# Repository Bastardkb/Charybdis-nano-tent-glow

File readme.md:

## Midglow plate

Charybdis Nano mod to add lights to the bottom plate when using the 30 degree organic tents.

## Required parts

### PCB

Order the PCB in 1mm thickness.
The gerber can be found in the releases section.

### Middle layer

The files are in the `mechanical` folder.

You have 2 options :

- print the STL in transparent PLA/PETG
- laser-cut an acrylic sheet (use the dxf)

### Bottom layer

Use the bottom plates for the tents from the Charybdis repo. Either 3d print or laser cut.

### Screws etc

The parts are for one side. If building a double Charybdis Nano, double the parts.

| Part name                                    | Amount |
| -------------------------------------------- | ------ |
| M4 8mm Torx Screw                            | 2      |
| M4 Nut                                       | 2      |
| PCB                                          | 1      |
| 3d printed or laser cut acrylic middle layer | 1      |
| 1206 resistor, 330 Ohms                      | 1      |
| 1206 capacitor, 1uF                          | 1      |
| SK6812 Mini_e led                            | 15     |

## License

This work is licensed under a Creative Commons Attribution-NonCommercial-ShareAlike 4.0 International License.

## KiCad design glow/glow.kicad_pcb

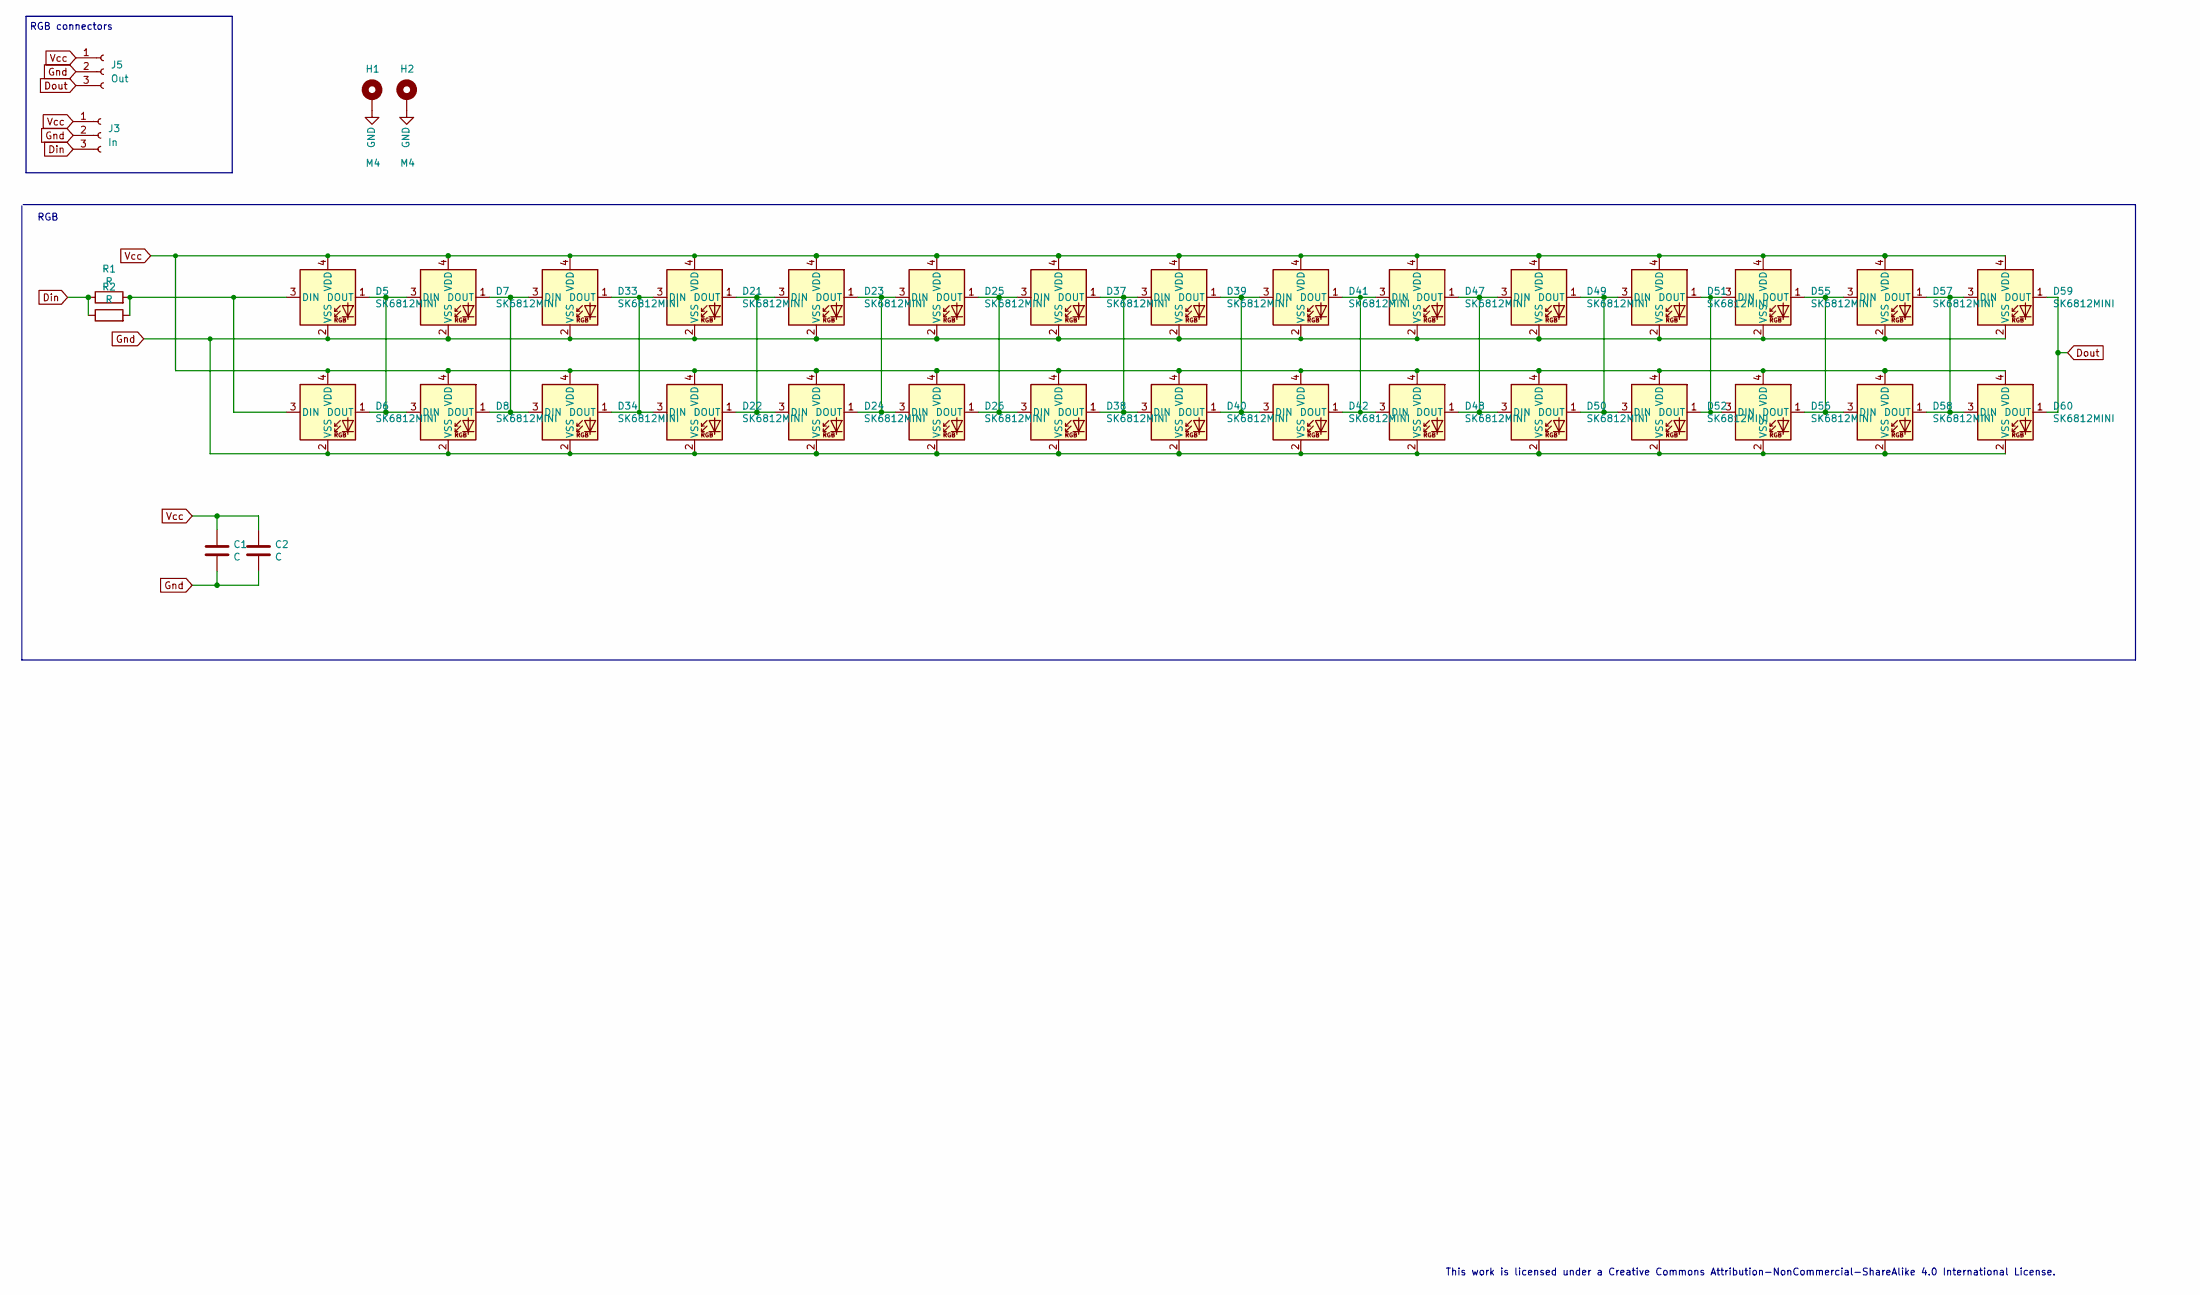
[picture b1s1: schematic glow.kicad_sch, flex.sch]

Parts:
C1, C2: C; C_1206_3216Metric_Pad1.42x1.75mm_HandSolder
D5, D7, D21, D23, D25, D33, D37, D39, D41, D47, D49, D51, D55, D57, D59: SK6812MINI; YS-SK6812MINI-E_REVERSE
D6, D8, D22, D24, D26, D34, D38, D40, D42, D48, D50, D52, D56, D58, D60: SK6812MINI; YS-SK6812MINI-E_REVERSE_NO_EDGECUT
H1, H2: M4; MountingHole_4mm_Pad_Via
J3: In; PinHeader_1x03_P2.54mm_Vertical
J5: Out; PinHeader_1x03_P2.54mm_Vertical
R1, R2: R; R_1206_3216Metric_Pad1.42x1.75mm_HandSolder

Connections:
Din: J3.3, R1.1, R2.1
Dout: D59.1 (DOUT), D60.1 (DOUT), J5.3
GND: H1.1, H2.1
Gnd: C1.2, C2.2, D5.2 (VSS), D6.2 (VSS), D7.2 (VSS), D8.2 (VSS), D21.2 (VSS), D22.2 (VSS), D23.2 (VSS), D24.2 (VSS), D25.2 (VSS), D26.2 (VSS), D33.2 (VSS), D34.2 (VSS), D37.2 (VSS), D38.2 (VSS), D39.2 (VSS), D40.2 (VSS), D41.2 (VSS), D42.2 (VSS), D47.2 (VSS), D48.2 (VSS), D49.2 (VSS), D50.2 (VSS), D51.2 (VSS), D52.2 (VSS), D55.2 (VSS), D56.2 (VSS), D57.2 (VSS), D58.2 (VSS), D59.2 (VSS), D60.2 (VSS), J3.2, J5.2
unnamed: D5.1 (DOUT), D6.1 (DOUT), D7.3 (DIN), D8.3 (DIN)
unnamed: D21.1 (DOUT), D22.1 (DOUT), D23.3 (DIN), D24.3 (DIN)
unnamed: D23.1 (DOUT), D24.1 (DOUT), D25.3 (DIN), D26.3 (DIN)
unnamed: D25.1 (DOUT), D26.1 (DOUT), D37.3 (DIN), D38.3 (DIN)
unnamed: D7.1 (DOUT), D8.1 (DOUT), D33.3 (DIN), D34.3 (DIN)
unnamed: D21.3 (DIN), D22.3 (DIN), D33.1 (DOUT), D34.1 (DOUT)
unnamed: D37.1 (DOUT), D38.1 (DOUT), D39.3 (DIN), D40.3 (DIN)
unnamed: D39.1 (DOUT), D40.1 (DOUT), D41.3 (DIN), D42.3 (DIN)
unnamed: D41.1 (DOUT), D42.1 (DOUT), D47.3 (DIN), D48.3 (DIN)
unnamed: D47.1 (DOUT), D48.1 (DOUT), D49.3 (DIN), D50.3 (DIN)
unnamed: D49.1 (DOUT), D50.1 (DOUT), D51.3 (DIN), D52.3 (DIN)
unnamed: D51.1 (DOUT), D52.1 (DOUT), D55.3 (DIN), D56.3 (DIN)
unnamed: D55.1 (DOUT), D56.1 (DOUT), D57.3 (DIN), D58.3 (DIN)
unnamed: D57.1 (DOUT), D58.1 (DOUT), D59.3 (DIN), D60.3 (DIN)
unnamed: D5.3 (DIN), D6.3 (DIN), R1.2, R2.2
Vcc: C1.1, C2.1, D5.4 (VDD), D6.4 (VDD), D7.4 (VDD), D8.4 (VDD), D21.4 (VDD), D22.4 (VDD), D23.4 (VDD), D24.4 (VDD), D25.4 (VDD), D26.4 (VDD), D33.4 (VDD), D34.4 (VDD), D37.4 (VDD), D38.4 (VDD), D39.4 (VDD), D40.4 (VDD), D41.4 (VDD), D42.4 (VDD), D47.4 (VDD), D48.4 (VDD), D49.4 (VDD), D50.4 (VDD), D51.4 (VDD), D52.4 (VDD), D55.4 (VDD), D56.4 (VDD), D57.4 (VDD), D58.4 (VDD), D59.4 (VDD), D60.4 (VDD), J3.1, J5.1

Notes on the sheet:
RGB connectors
RGB
This work is licensed under a Creative Commons Attribution-NonCommercial-ShareAlike 4.0 International License.

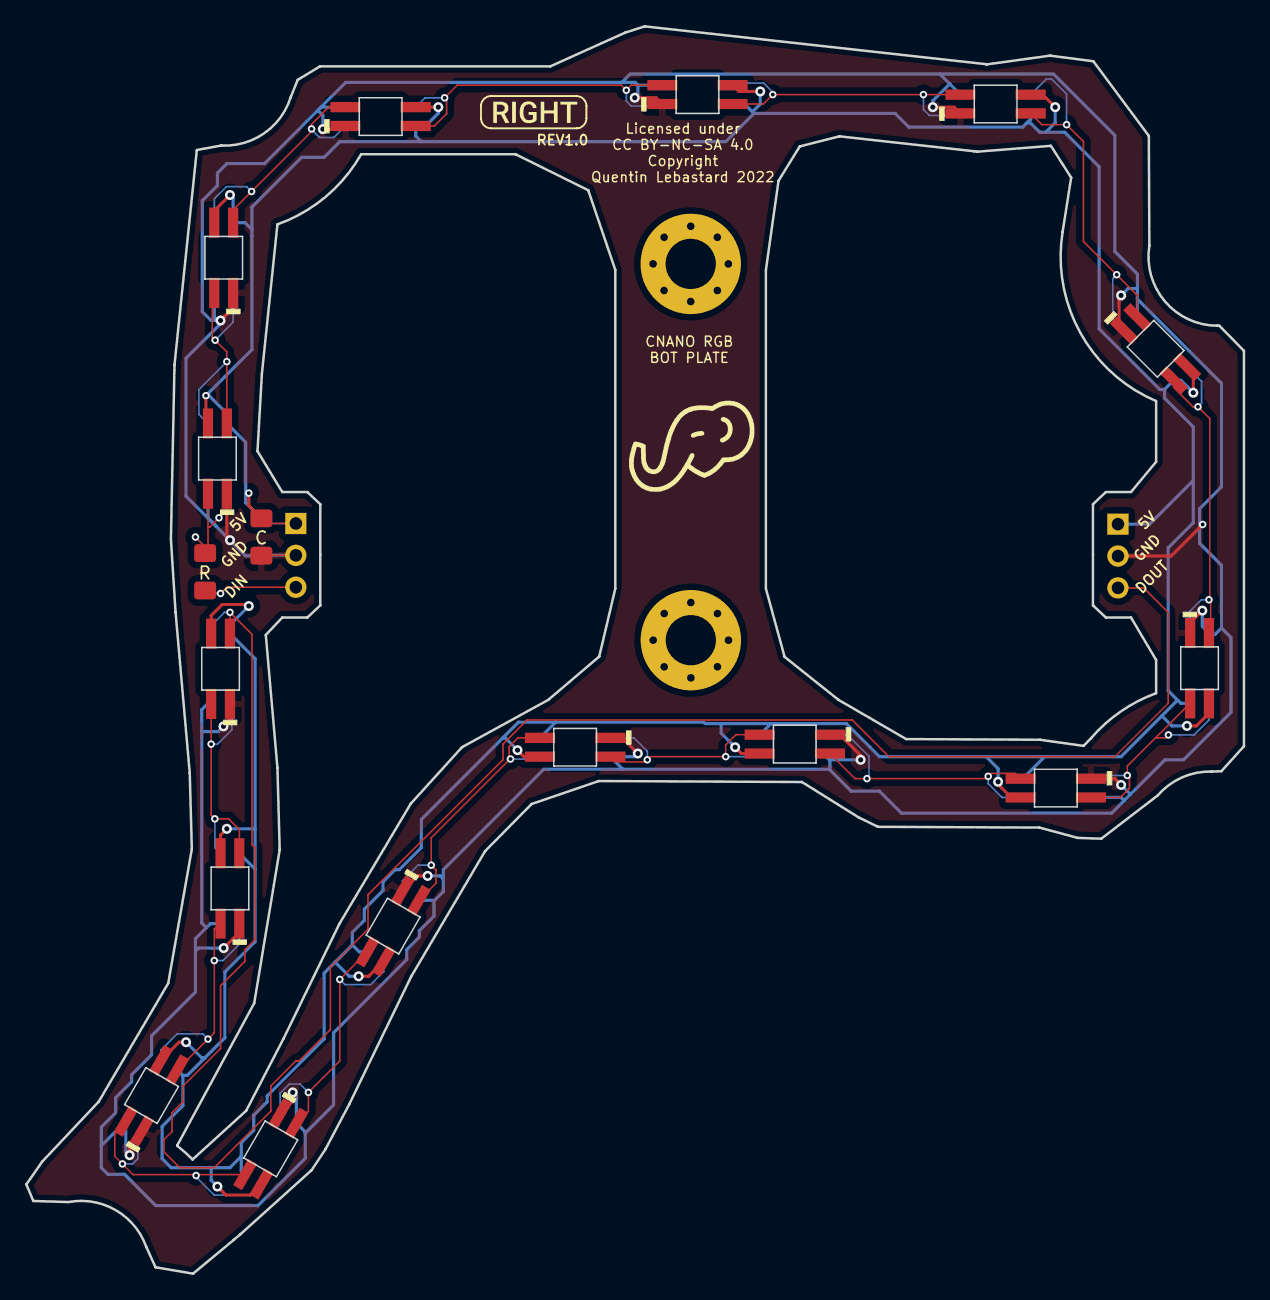
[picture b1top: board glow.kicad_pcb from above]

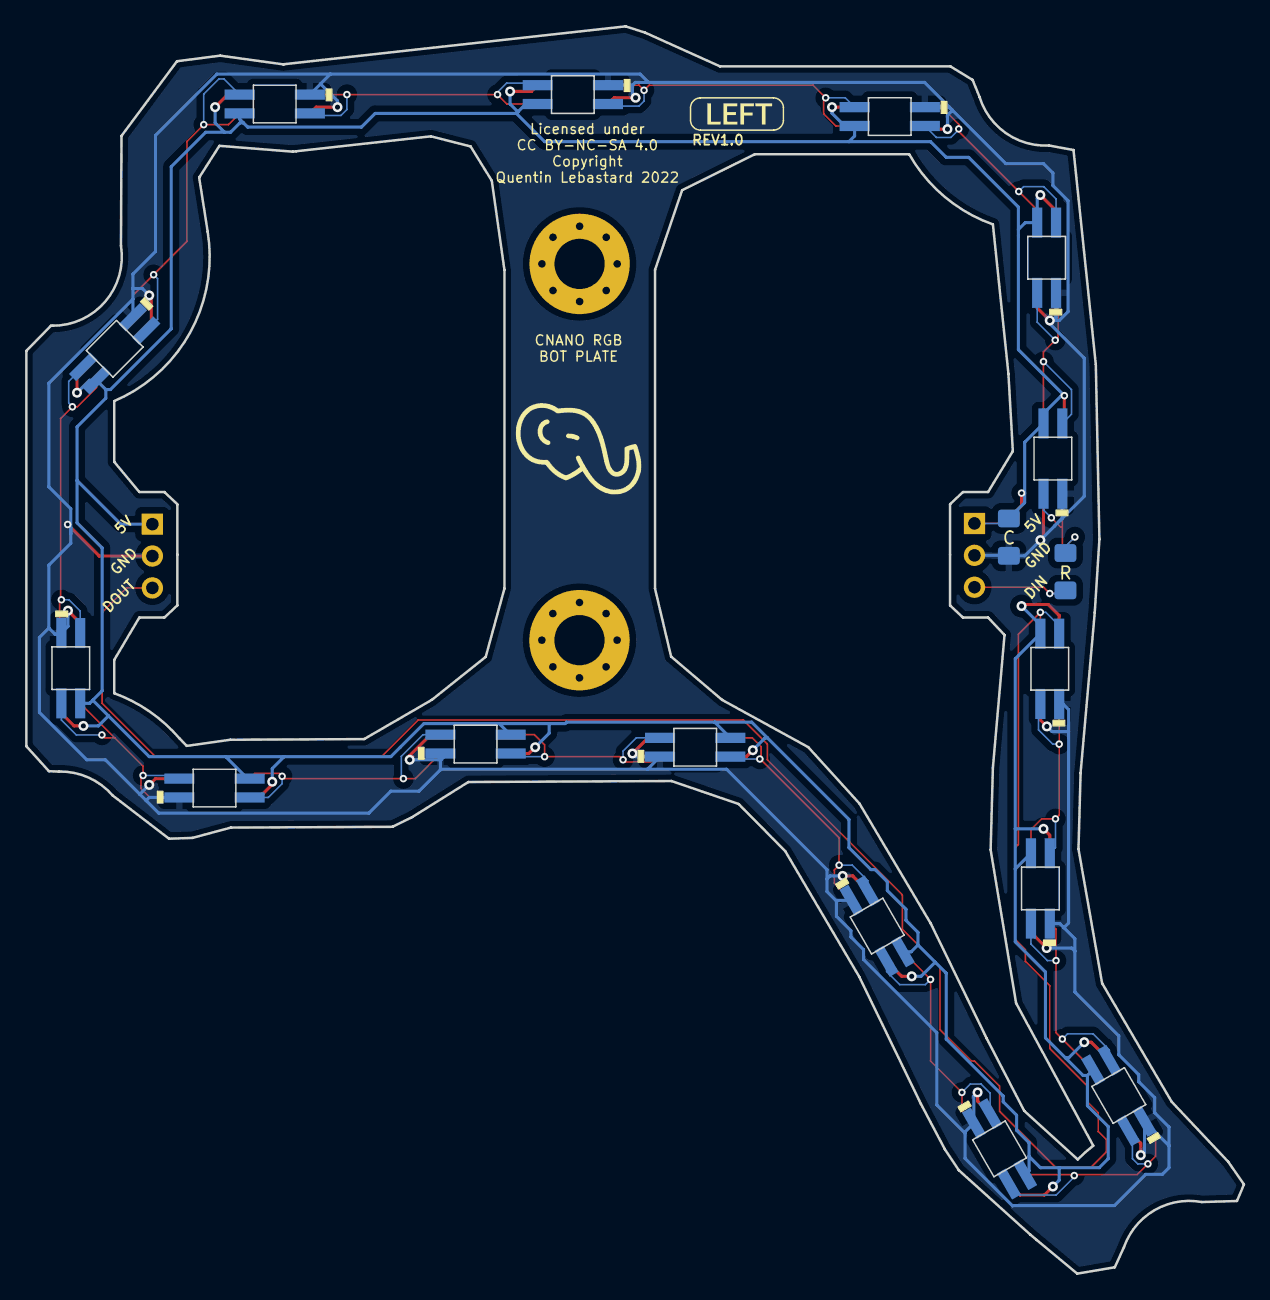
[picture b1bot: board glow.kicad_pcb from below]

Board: 2 copper layers, 97.0 x 99.4 mm, 40 parts (18 on the bottom side), 20 nets.

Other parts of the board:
kibuzzard-61F01B61: G***; kibuzzard-61F01B61
kibuzzard-6208EFFE: G***; kibuzzard-6208EFFE

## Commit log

2022-02-18 start
2022-02-18 routing
2022-02-19 routing, logos
2022-03-21 add license
2022-03-21 prepare for OS

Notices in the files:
glow/glow.kicad_pcb:
CC BY-NC-SA 4.0
glow/glow.kicad_sch:
Copyright Quentin Lebastard 2022
